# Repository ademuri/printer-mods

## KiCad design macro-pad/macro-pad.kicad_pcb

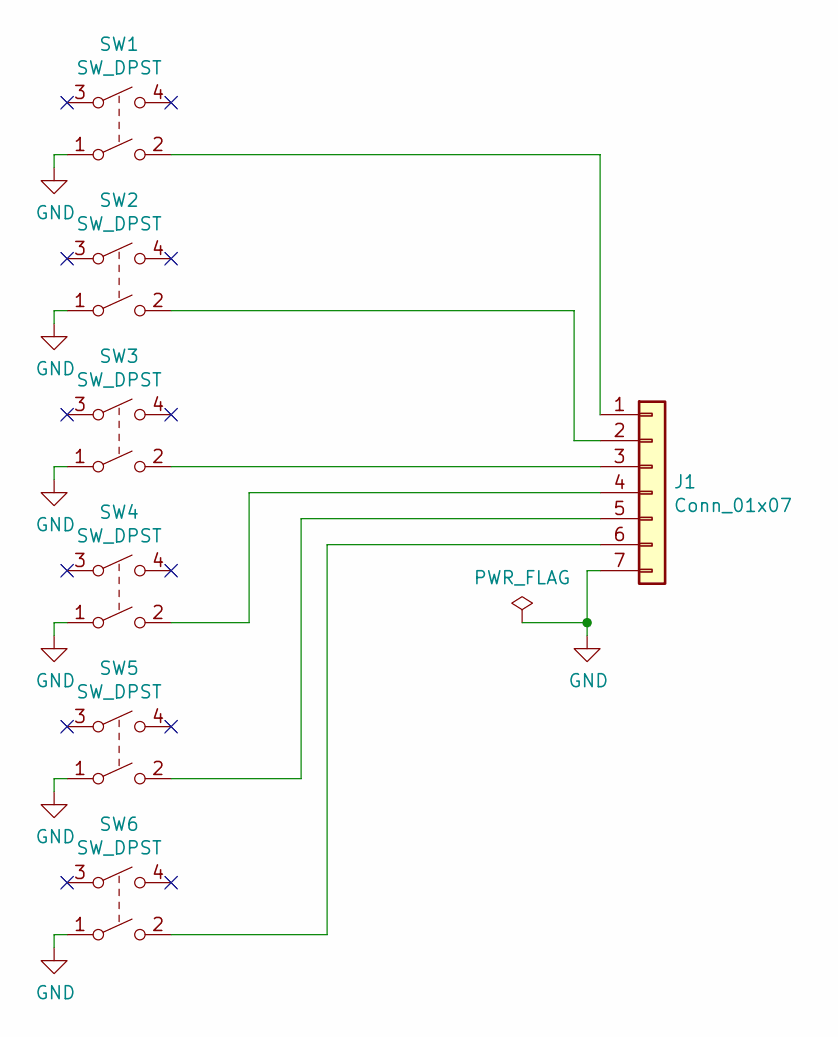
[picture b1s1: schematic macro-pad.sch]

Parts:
J1: Conn_01x07; PinHeader_1x07_P2.54mm_Vertical
SW1, SW2, SW3, SW4, SW5, SW6: SW_DPST; SW_TH_Tactile_Omron_B3F-10xx

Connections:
GND: J1.7, SW1.1, SW2.1, SW3.1, SW4.1, SW5.1, SW6.1
unnamed: J1.1, SW1.2
unnamed: J1.2, SW2.2
unnamed: J1.3, SW3.2
unnamed: J1.4, SW4.2
unnamed: J1.5, SW5.2
unnamed: J1.6, SW6.2

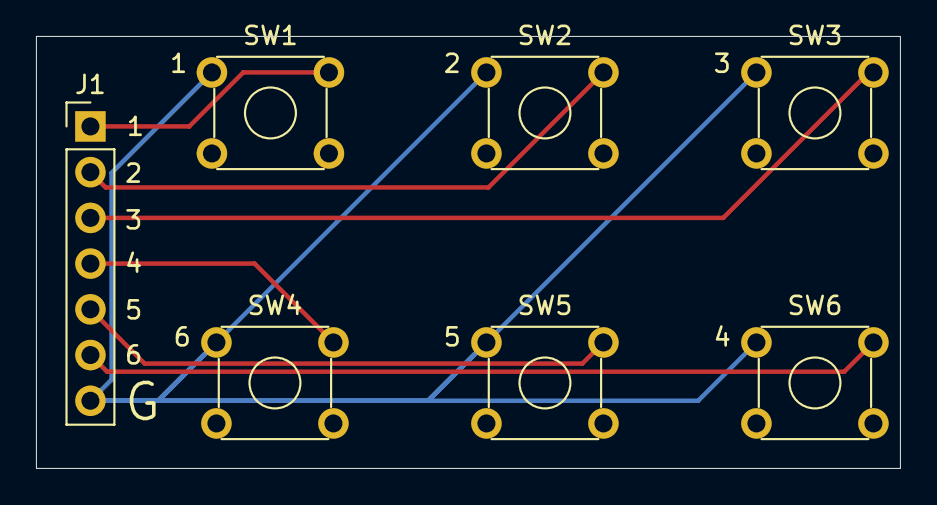
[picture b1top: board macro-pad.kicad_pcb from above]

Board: 2 copper layers, 48.0 x 24.0 mm, 7 parts (0 on the bottom side), 7 nets.

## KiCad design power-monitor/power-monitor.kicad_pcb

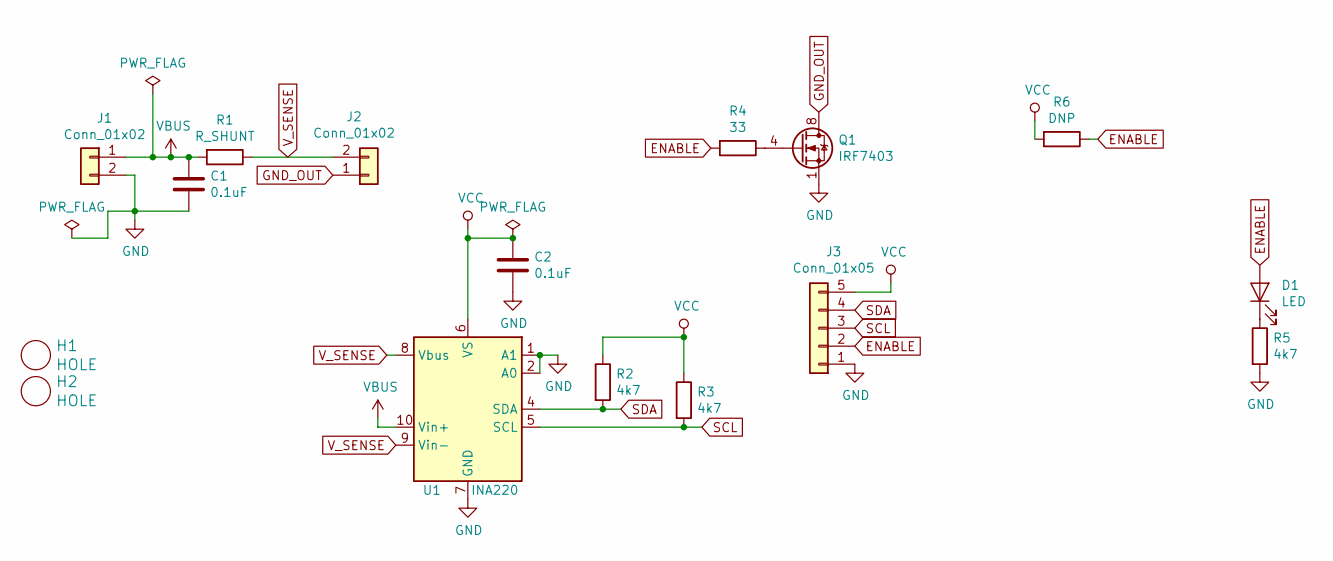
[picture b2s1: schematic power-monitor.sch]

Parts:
C1, C2: 0.1uF; C_0603_1608Metric_Pad1.05x0.95mm_HandSolder
D1: LED; LED_0805_2012Metric_Pad1.15x1.40mm_HandSolder
H1, H2: HOLE; MountingHole_3.2mm_M3
J1, J2: Conn_01x02; Wurth_ScrewTerminal_1x02_P5.00mm_691137710002
J3: Conn_01x05; PinHeader_1x05_P2.54mm_Vertical
Q1: IRF7403; SOIC-8_3.9x4.9mm_P1.27mm
R1: R_SHUNT; R_1206_3216Metric_Pad1.42x1.75mm_HandSolder
R2, R3, R5: 4k7; R_0805_2012Metric_Pad1.15x1.40mm_HandSolder
R4: 33; R_0805_2012Metric_Pad1.15x1.40mm_HandSolder
R6: DNP; R_0402_1005Metric
U1: INA220; VSSOP-10_3x3mm_P0.5mm

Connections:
ENABLE: D1.2 (A), J3.2, R4.2, R6.1
GND: C1.2, C2.2, J1.2, J3.1, Q1.1 (S), Q1.2 (S), Q1.3 (S), R5.2, U1.1 (A1), U1.2 (A0), U1.7 (GND)
GND_OUT: J2.1, Q1.5 (D), Q1.6 (D), Q1.7 (D), Q1.8 (D)
unnamed: D1.1 (K), R5.1
unnamed: Q1.4 (G), R4.1
SCL: J3.3, R3.2, U1.5 (SCL)
SDA: J3.4, R2.2, U1.4 (SDA)
VBUS: C1.1, J1.1, R1.2, U1.10 (Vin+)
VCC: C2.1, J3.5, R2.1, R3.1, R6.2, U1.6 (VS)
V_SENSE: J2.2, R1.1, U1.8 (Vbus), U1.9 (Vin-)

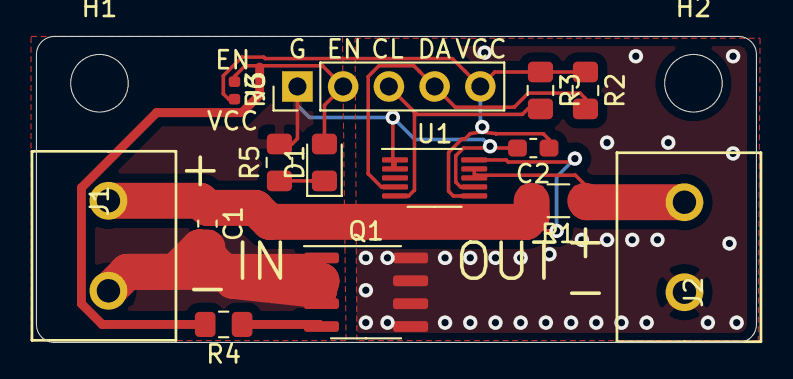
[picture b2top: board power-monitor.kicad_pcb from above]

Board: 2 copper layers, 40.0 x 17.0 mm, 16 parts (0 on the bottom side), 10 nets.

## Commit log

2021-10-23 Add power monitor v1.0
2021-11-19 Fix soldermask clearance
2021-11-20 Add macro pad
